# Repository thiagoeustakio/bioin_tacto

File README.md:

# BioIn-Tacto: A Compliant Multimodal Tactile Sensing Module
Hardware X journal paper: [BioIn-Tacto: A Compliant Multimodal Tactile Sensing Module]()

How to cite this repository:

    @software{thiago_eustaquio_alves_de_oliveira_2022_7011242,
      author       = {Thiago Eustaquio Alves de Oliveira and
                      Vinicius Prado da Fonseca},
      title        = {{BioIn-Tacto: tactile sensing module design files 
                       and source code.}},
      month        = aug,
      year         = 2022,
      publisher    = {Zenodo},
      version      = {v1.0.0},
      doi          = {10.5281/zenodo.7011242},
      url          = {https://doi.org/10.5281/zenodo.7011242}
    }

## Overview

This repository contain firmware, ROS code and CAD files for the multimodal tactile sensor. The packages have been tested under ROS Melodic and Ubuntu 18.04 LTS.

- ROS code is in the [bioin_tacto_ws](bioin_tacto_ws/) folder.  
- Sensor building CAD files are upload in the [CAD](CAD/) folder.  
- Firmware files are available in the [firmware](firmware/) folder.

This sensing module was developed with a focus on the compliant structure and skin deformation. This module is a research platform that can be built at a lower price (approximately **USD$ 35.00**, using only 3D printing) than other similar sensors. Moreover, it was designed to capture the skin deformation not available on most tactile sensors in the market.

**Authors: [Thiago Eustaquio Alves de Oliveira](https://www.linkedin.com/in/teado/), talvesd@lakeheadu.ca and [Vinicius Prado da Fonseca](https://www.cs.mun.ca/~vpradodafons/), vpradodafons@mun.ca**

**Affiliation: Department of Computer Science, [Lakehead University](https://www.lakeheadu.ca/), Canada; Department of Computer Science [Memorial University of Newfoundland](https://www.mun.ca/), Canada**

## Installation
- Before do this, please backup important files.
- After following building instructions found in Section 5 from the Hardware X journal paper, [BioIn-Tacto: A Compliant Multimodal Tactile Sensing Module]() you should have a working sensor module that requires a firmware upload to the MCU for serial communication with the main computer.

### Dependencies

- Tested using Ubuntu 18.04.
- Tested using Teensy 4.0 MCU.

## Firmware Installation

The firmware requires the Arduino environemnt and ROS messages from the [bioin_tacto_ws](bioin_tacto_ws/). The following section covers, Arduino, teensyduino, ROS messages and firmware upload instructions.

## Install Arduino and Teensyduino
Follow the **Command Line Install** instructions below, also available [here](https://www.pjrc.com/teensy/td_download.html).

    $ wget https://downloads.arduino.cc/arduino-1.8.15-linux64.tar.xz
    $ wget https://www.pjrc.com/teensy/td_154/TeensyduinoInstall.linux64
    $ wget https://www.pjrc.com/teensy/00-teensy.rules
    $ sudo cp 00-teensy.rules /etc/udev/rules.d/
    $ tar -xf arduino-1.8.15-linux64.tar.xz
    $ chmod 755 TeensyduinoInstall.linux64
    $ ./TeensyduinoInstall.linux64 --dir=arduino-1.8.15
    $ cd arduino-1.8.15/hardware/teensy/avr/cores/teensy4
    $ make

## Install ROS (Melodic) tested on Ubuntu 18.04
This software is built on the Robotic Operating System ([ROS](http://wiki.ros.org/ROS/Installation)).   
Follow **Desktop-Full Install: (Recommended)** below, also available [here](http://wiki.ros.org/melodic/Installation/Ubuntu).

    $ sudo sh -c 'echo "deb http://packages.ros.org/ros/ubuntu $(lsb_release -sc) main" > /etc/apt/sources.list.d/ros-latest.list'
    $ sudo apt install curl
    $ curl -s https://raw.githubusercontent.com/ros/rosdistro/master/ros.asc | sudo apt-key add -
    $ sudo apt update
    $ sudo apt upgrade
    $ sudo apt install ros-melodic-desktop-full 
    $ echo "source /opt/ros/melodic/setup.bash" >> ~/.bashrc
    $ source ~/.bashrc
    $ sudo apt install python-rosdep python-rosinstall python-rosinstall-generator python-wstool build-essential
    $ sudo apt install python-rosdep
    $ sudo rosdep init
    $ rosdep update

## Compile the ros `bioin_tacto_ws` and messages

    $ cd <repository_folder>/bioin_tacto_ws/
    $ catkin_make
    $ source devel/setup.bash

## Generate arduino `ros_lib` library with ROS messages from workspace

    $ cd <arduino_directory>/libraries
    $ rm -rf ros_lib
    $ rosrun rosserial_arduino make_libraries.py .

## Tactile module firmware instalation

- Copy firmware/lib/**MPL115A2MUX** folder to `<arduino_directory>/libraries`
- Copy firmware/lib/**LSMMUX** folder to `<arduino_directory>/libraries`
- Copy firmware/lib/**SparkFun_BNO080_Cortex_Based_IMU** folder to `<arduino_directory>/libraries`
- Inside the arduino environemnt open the **firmware/bioin-tacto-firmware/LSM9DS0/bioin-tacto-firmware/bioin-tacto-firmware.ino** file, compile and upload to the teensy
- OR, if you are using the BNO08X Custom MARG, open the **firmware/bioin-tacto-firmware/BNO08X/bioin-tacto-firmware_BNO08X/bioin-tacto-firmware_BNO08X.ino** file in the arduino environemnt, compile and upload to the teensy

This firmware was tested using [teensy 4.0](https://www.pjrc.com/store/teensy40.html)

## How to start?
Launch the module nodes and visualization

    $ roslaunch bioin_tacto cell0.launch
    OR
    $ roslaunch bioin_tacto cell0_BNO08X.launch

## Description

### Visualize sensor data with `rqt` or `rostopic list`

The following topics are available in rqt (rostopic list)

    $ rostopic list
    /imu/data
    /imu/data_raw
    /imu/mag
    /m_imus_bias_removed
    /m_imus_serial
    /raw_barometers_teensy
    /raw_imus_teensy
    /tf

### Visualize sensor data with `rviz`

RViz will open automatically after the cell0.launch is launched.
You can visualize the frames of refence and pressure level on a rviz marker.

## Validation and Characterization

- The multimodal tactile sensor validation and characterization, click image to the YouTube video.

## Demo

- The multimodal tactile sensor used in surface reconstruction, click image to the YouTube video.

## License

See LICENSE file.

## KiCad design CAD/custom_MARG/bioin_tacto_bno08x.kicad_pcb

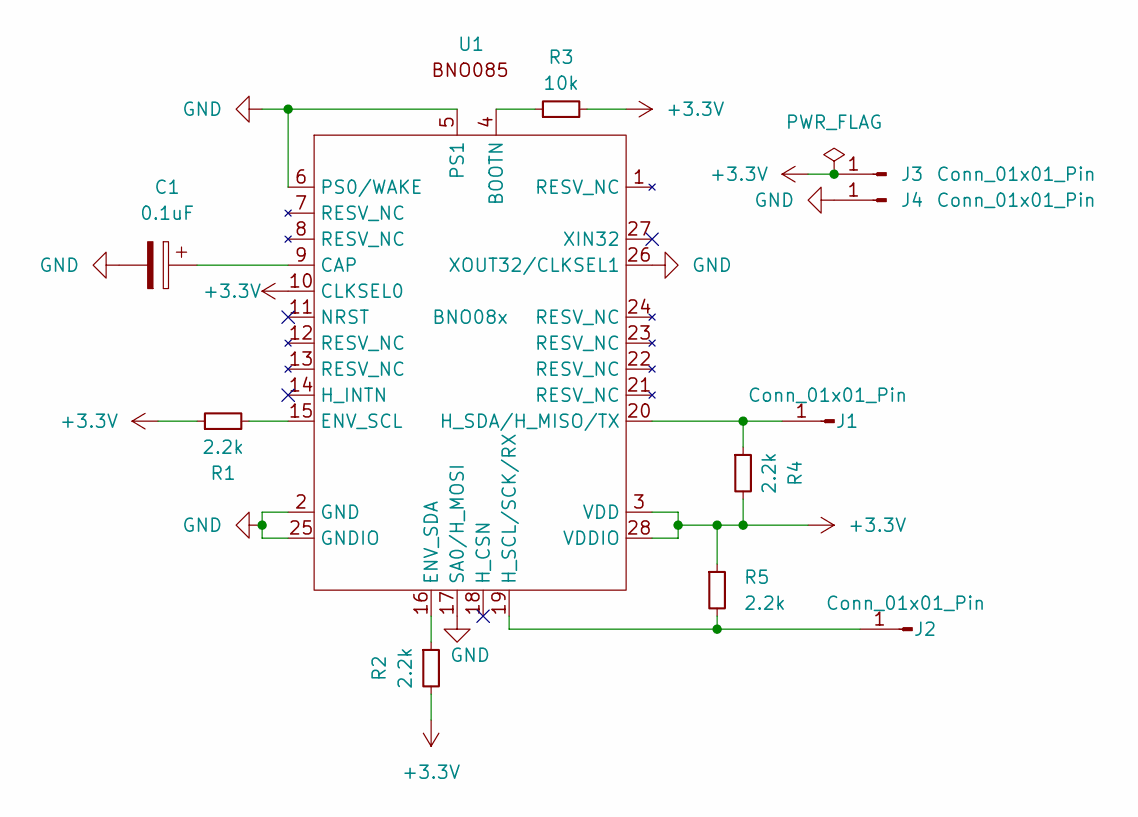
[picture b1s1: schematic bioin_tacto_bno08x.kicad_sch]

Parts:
C1: 0.1uF; C_0402_1005Metric
J1, J2, J3, J4: Conn_01x01_Pin; PinHeader_1x01_P1.00mm_Vertical
R1, R2, R4, R5: 2.2k; R_0402_1005Metric
R3: 10k; R_0402_1005Metric
U1: BNO08x; LGA-28_5.2x3.8mm_P0.5mm

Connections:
+3.3V: J3.1, R1.1, R2.2, R3.2, R4.2, R5.1, U1.3 (VDD), U1.10 (CLKSEL0), U1.28 (VDDIO)
GND: C1.2, J4.1, U1.2 (GND), U1.5 (PS1), U1.6 (PS0/WAKE), U1.17 (SA0/H_MOSI), U1.25 (GNDIO), U1.26 (XOUT32/CLKSEL1)
unnamed: J1.1, R4.1, U1.20 (H_SDA/H_MISO/TX)
unnamed: J2.1, R5.2, U1.19 (H_SCL/SCK/RX)
unnamed: R3.1, U1.4 (BOOTN)
unnamed: C1.1, U1.9 (CAP)
unnamed: R1.2, U1.15 (ENV_SCL)
unnamed: R2.1, U1.16 (ENV_SDA)

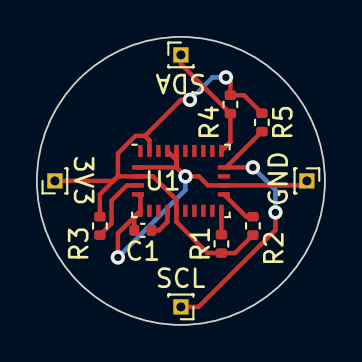
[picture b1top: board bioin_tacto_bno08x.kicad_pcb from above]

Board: 2 copper layers, 16.0 x 16.0 mm, 11 parts (0 on the bottom side), 8 nets.

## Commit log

2022-08-19 fixed minor TODOs
2023-08-11 Adding custom MARG bno08x PCB design files
2023-08-12 Add support for the BNO08X Custom MARG
